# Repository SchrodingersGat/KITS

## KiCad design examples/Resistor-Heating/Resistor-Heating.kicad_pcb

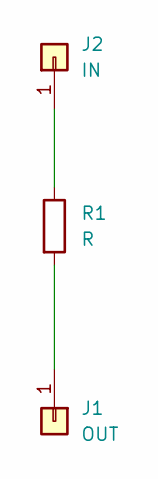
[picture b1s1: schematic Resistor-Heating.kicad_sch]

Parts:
J1: OUT; TestPoint_Pad_D2.0mm
J2: IN; TestPoint_Pad_D2.0mm
R1: R; R_0805_2012Metric

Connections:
unnamed: J1.1 (Pin_1_1), R1.2
unnamed: J2.1 (Pin_1_1), R1.1

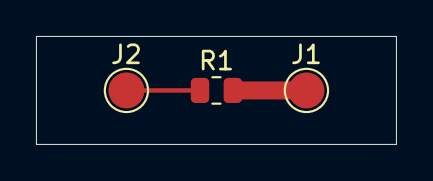
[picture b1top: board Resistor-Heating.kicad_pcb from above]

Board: 2 copper layers, 20.0 x 6.0 mm, 3 parts (0 on the bottom side), 2 nets.

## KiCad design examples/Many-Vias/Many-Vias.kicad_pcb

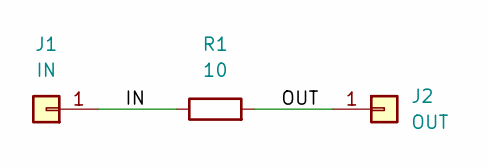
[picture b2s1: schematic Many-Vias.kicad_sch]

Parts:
J1: IN; TestPoint_Pad_4.0x4.0mm
J2: OUT; TestPoint_Pad_4.0x4.0mm
R1: 10; R_4020_10251Metric

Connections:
/IN: J1.1 (Pin_1_1), R1.1
/OUT: J2.1 (Pin_1_1), R1.2

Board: 4 copper layers, 3 parts (1 on the bottom side), 2 nets, no tracks yet.

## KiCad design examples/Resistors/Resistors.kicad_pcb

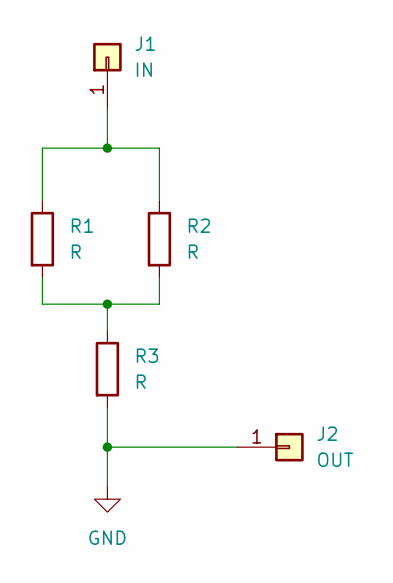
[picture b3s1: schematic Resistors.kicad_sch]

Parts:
J1: IN; TestPoint_Loop_D3.80mm_Drill2.0mm
J2: OUT; TestPoint_Loop_D3.80mm_Drill2.0mm
R1, R2, R3: R; R_0805_2012Metric

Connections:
GND: J2.1 (Pin_1_1), R3.2
unnamed: J1.1 (Pin_1_1), R1.1, R2.1
unnamed: R1.2, R2.2, R3.1

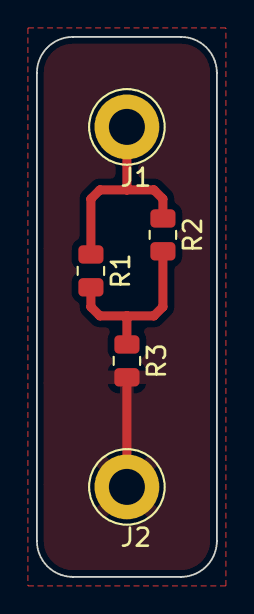
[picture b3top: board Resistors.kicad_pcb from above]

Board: 2 copper layers, 10.0 x 30.0 mm, 5 parts (0 on the bottom side), 3 nets.
